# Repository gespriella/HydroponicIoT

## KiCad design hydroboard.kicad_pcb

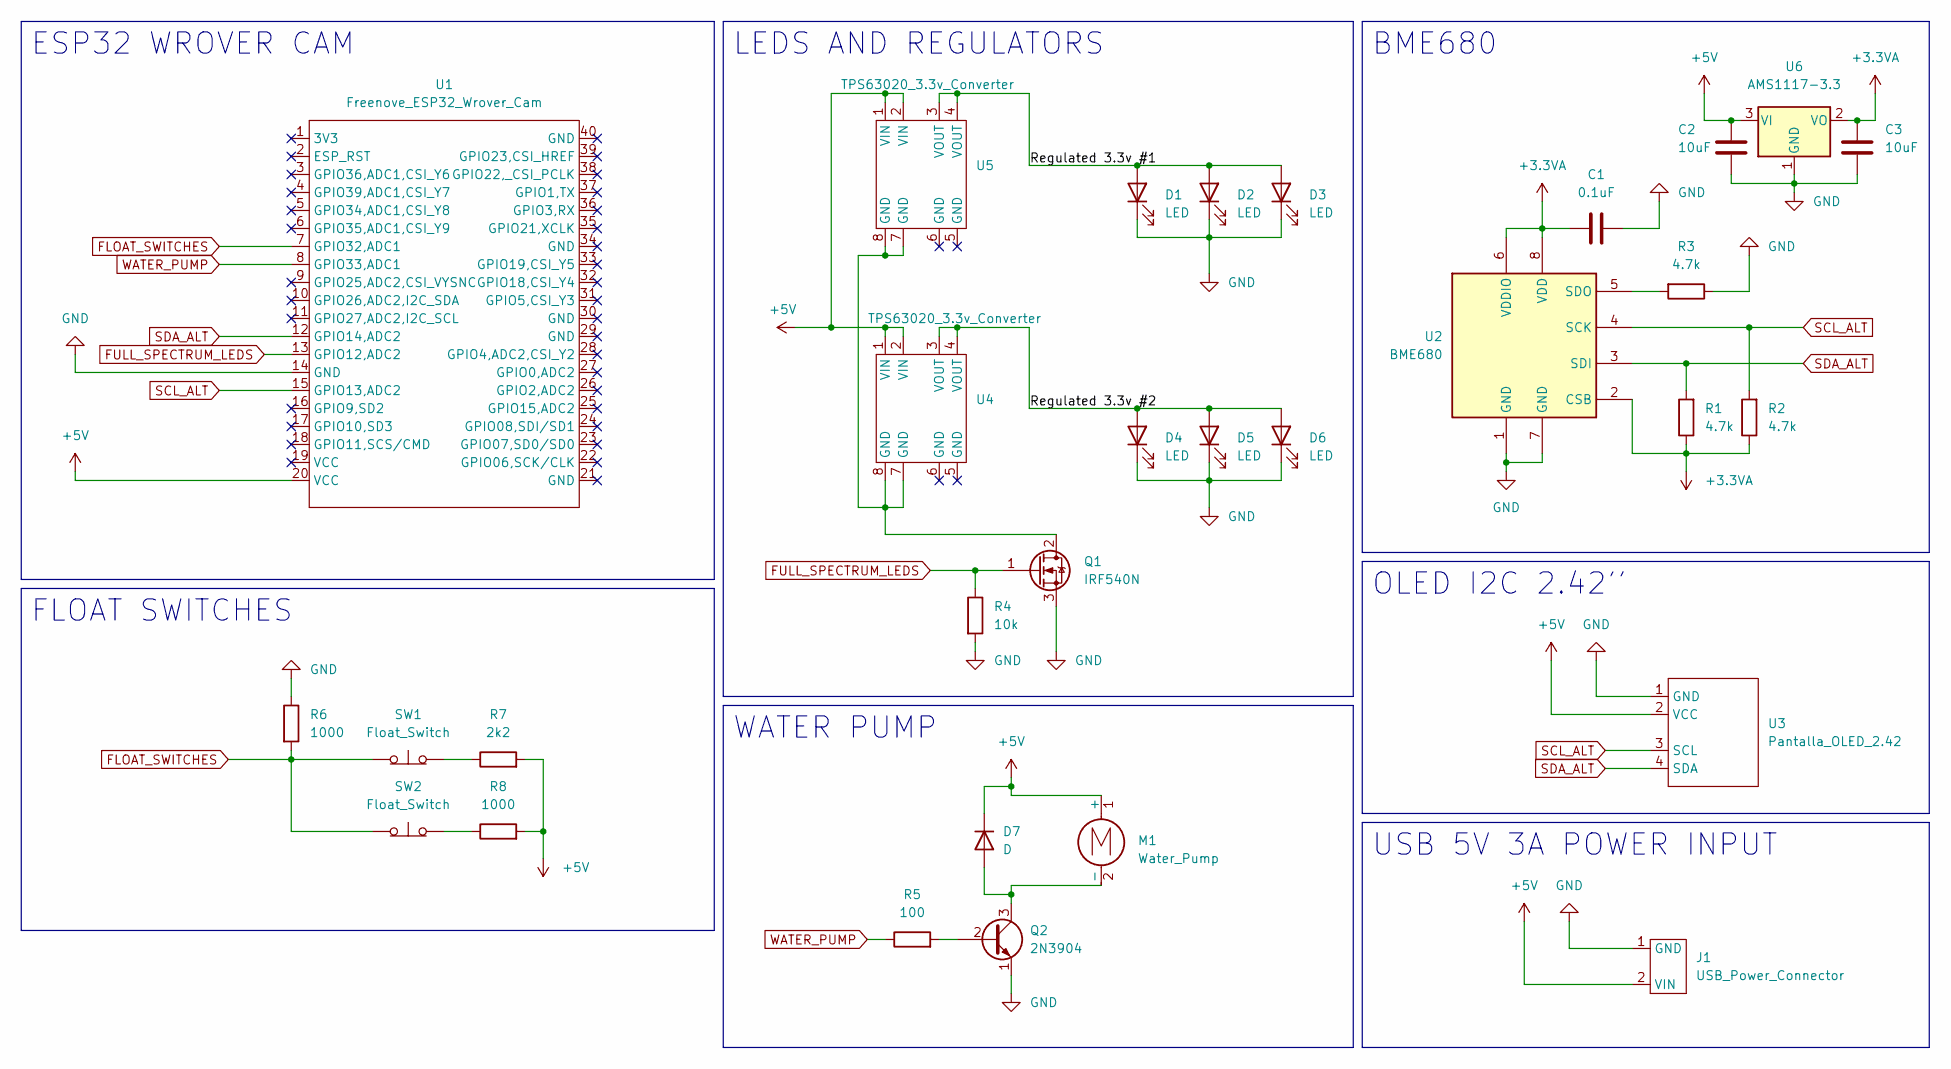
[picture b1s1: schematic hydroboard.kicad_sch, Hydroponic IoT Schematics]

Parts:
C1: 0.1uF; C_0805_2012Metric
C2, C3: 10uF; C_0805_2012Metric
D1, D2, D3, D4, D5, D6: LED; PinSocket_1x02_P2.54mm_Vertical
D7: D; D_0805_2012Metric
J1: USB_Power_Connector; PinHeader_1x02_P2.54mm_Vertical
M1: Water_Pump; PinHeader_1x02_P2.54mm_Vertical
Q1: IRF540N; TO-220-3_Vertical
Q2: 2N3904; SOT-23
R1, R2, R3: 4.7k; R_0805_2012Metric
R4: 10k; R_0805_2012Metric
R5: 100; R_0805_2012Metric
R6, R8: 1000; R_0805_2012Metric
R7: 2k2; R_0805_2012Metric
SW1, SW2: Float_Switch; PinSocket_1x02_P2.54mm_Vertical
U1: Freenove_ESP32_Wrover_Cam; Freenove ESP32 Wrover Cam
U2: BME680; Bosch_LGA-8_3x3mm_P0.8mm_ClockwisePinNumbering
U3: Pantalla_OLED_2.42; PinSocket_1x04_P2.54mm_Vertical
U4, U5: TPS63020_3.3v_Converter; Rakstore TPS63020 5v to 3.3v
U6: AMS1117-3.3; SOT-223-3_TabPin2

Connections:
+3.3VA: C1.1, C3.2, R1.1, R2.1, U2.2 (CSB), U2.6 (VDDIO), U2.8 (VDD), U6.2 (VO)
+5V: C2.2, D7.1 (K), J1.2 (VIN), M1.1 (+), R7.2, R8.2, U1.20 (VCC), U3.2 (VCC), U4.1 (VIN), U4.2 (VIN), U5.1 (VIN), U5.2 (VIN), U6.3 (VI)
/Regulated 3.3v #1: D1.2 (A), D2.2 (A), D3.2 (A), U5.3 (VOUT), U5.4 (VOUT)
/Regulated 3.3v #2: D4.2 (A), D5.2 (A), D6.2 (A), U4.3 (VOUT), U4.4 (VOUT)
FLOAT_SWITCHES: R6.2, SW1.1 (A), SW2.1 (A), U1.7 (GPIO32,ADC1)
FULL_SPECTRUM_LEDS: Q1.1 (G), R4.1, U1.13 (GPIO12,ADC2)
GND: C1.2, C2.1, C3.1, D1.1 (K), D2.1 (K), D3.1 (K), D4.1 (K), D5.1 (K), D6.1 (K), J1.1 (GND), Q1.3 (S), Q2.1 (E), R3.1, R4.2, R6.1, U1.14 (GND), U2.1 (GND), U2.7 (GND), U3.1 (GND), U6.1 (GND)
unnamed: D7.2 (A), M1.2 (-), Q2.3 (C)
unnamed: Q1.2 (D), U4.7 (GND), U4.8 (GND), U5.7 (GND), U5.8 (GND)
unnamed: Q2.2 (B), R5.2
unnamed: R3.2, U2.5 (SDO)
unnamed: R7.1, SW1.2 (B)
unnamed: R8.1, SW2.2 (B)
SCL_ALT: R2.2, U1.15 (GPIO13,ADC2), U2.4 (SCK), U3.3 (SCL)
SDA_ALT: R1.2, U1.12 (GPIO14,ADC2), U2.3 (SDI), U3.4 (SDA)
WATER_PUMP: R5.1, U1.8 (GPIO33,ADC1)

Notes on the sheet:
OLED I2C 2.42''
FLOAT SWITCHES
ESP32 WROVER CAM
WATER PUMP
BME680
LEDS AND REGULATORS
USB 5V 3A POWER INPUT

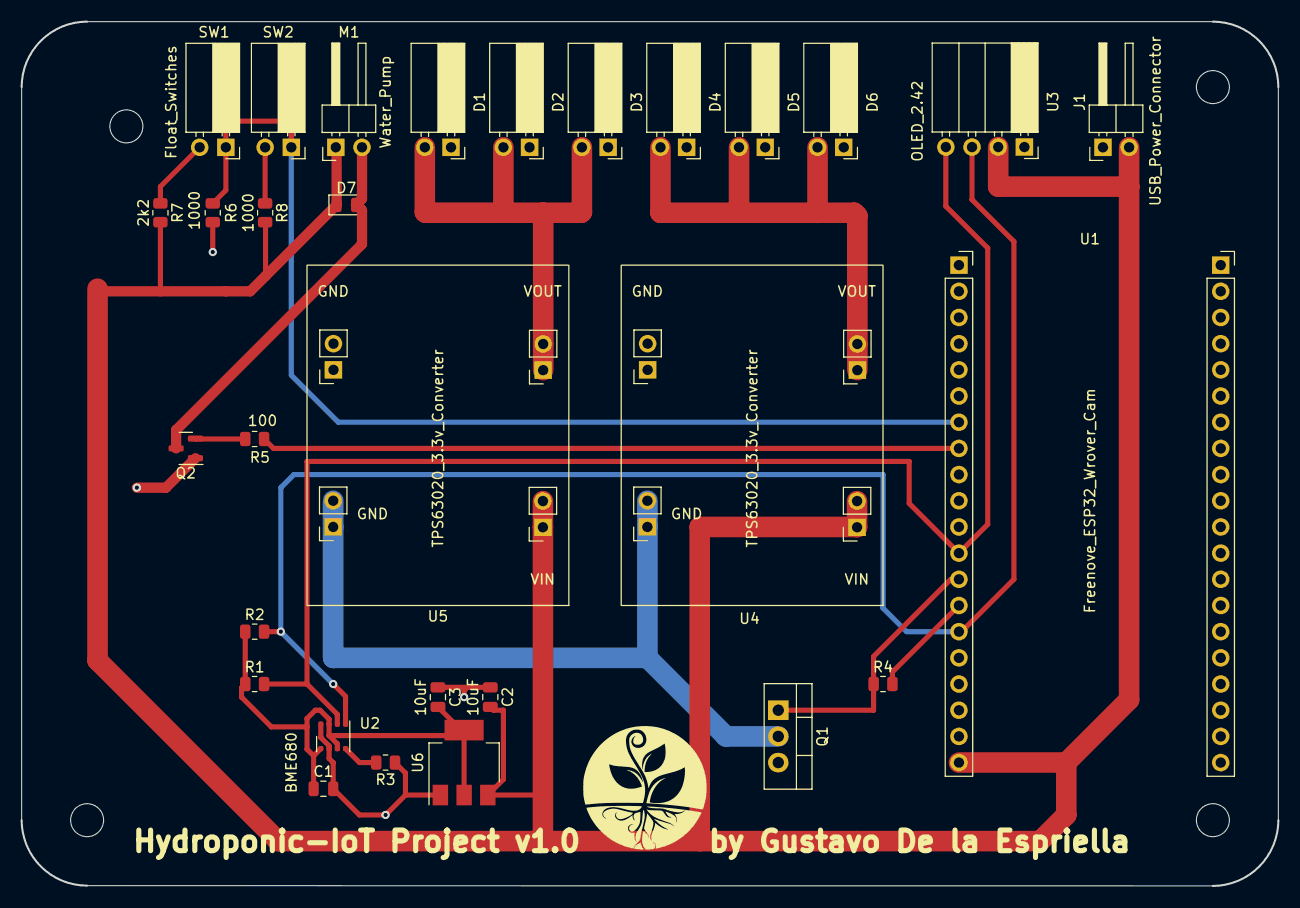
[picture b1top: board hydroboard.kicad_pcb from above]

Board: 2 copper layers, 121.9 x 83.9 mm, 30 parts (0 on the bottom side), 16 nets.
